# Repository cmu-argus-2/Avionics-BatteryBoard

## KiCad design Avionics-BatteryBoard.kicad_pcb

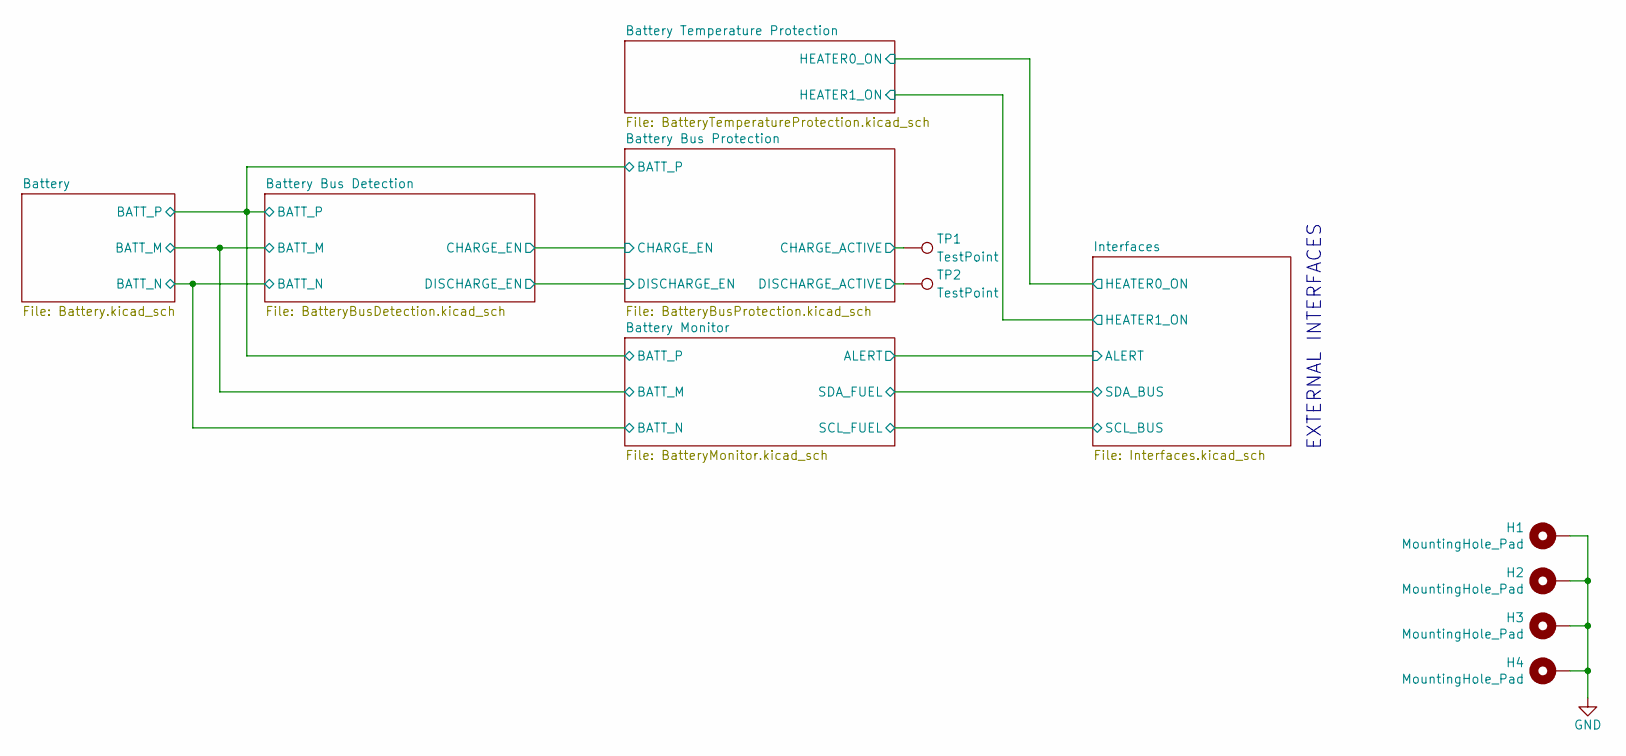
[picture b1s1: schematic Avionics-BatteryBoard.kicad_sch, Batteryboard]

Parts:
H1, H2, H3, H4: MountingHole_Pad; MountingHole_3.2mm_M3_Pad_Via
TP1, TP2: TestPoint; TestPoint_Pad_D1.5mm

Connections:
/Battery Bus Protection/CHARGE_ACTIVE: TP1.1 (1_1); also elsewhere on the board
/Battery Bus Protection/DISCHARGE_ACTIVE: TP2.1 (1_1); also elsewhere on the board
GND: H1.1 (1_1), H2.1 (1_1), H3.1 (1_1), H4.1 (1_1); also elsewhere on the board

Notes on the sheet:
EXTERNAL INTERFACES

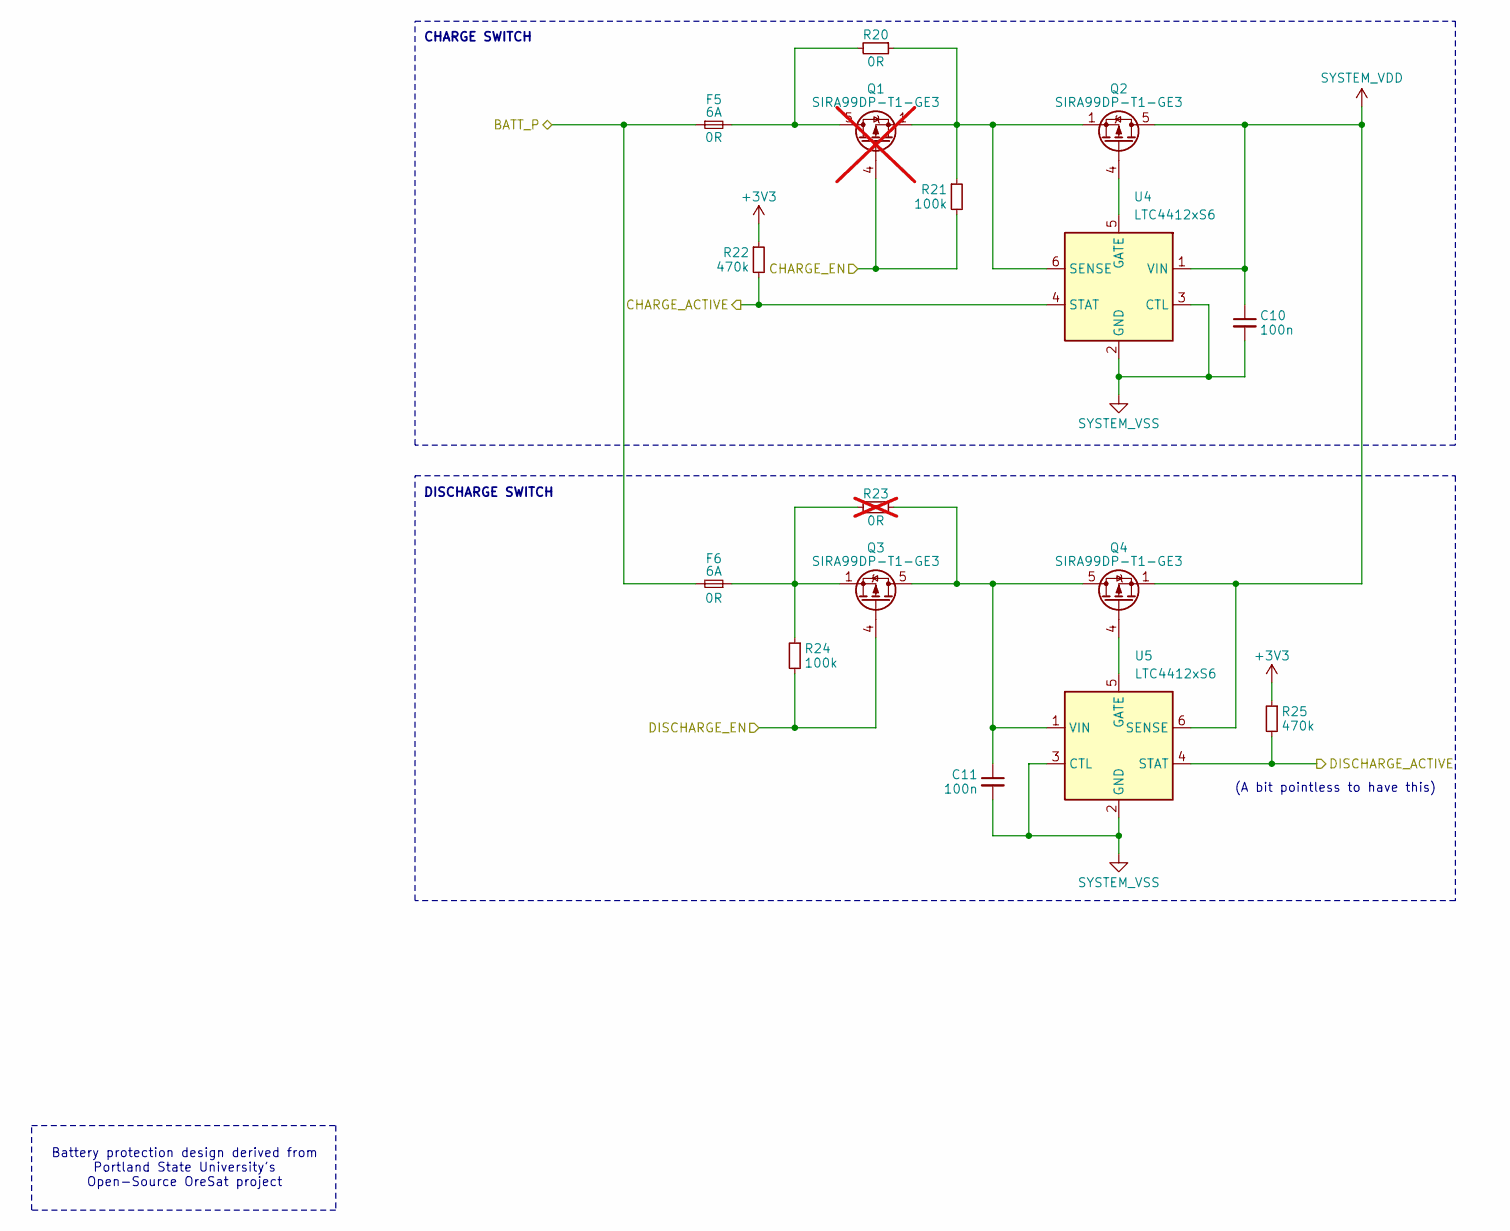
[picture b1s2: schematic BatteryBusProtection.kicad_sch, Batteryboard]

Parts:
C10, C11: 100n; C_0603_1608Metric; MPN C307348
F5, F6: 6A; Fuse_1206_3216Metric; MPN C844862
Q1: SIRA99DP-T1-GE3; PowerPAK_SO-8_Single; MPN C3289459; not fitted
Q2, Q3, Q4: SIRA99DP-T1-GE3; PowerPAK_SO-8_Single; MPN C3289459
R20: 0R; R_1206_3216Metric; MPN C237792
R21, R24: 100k; R_0603_1608Metric; MPN C237792
R22, R25: 470k; R_0603_1608Metric; MPN C138280
R23: 0R; R_1206_3216Metric; MPN C237792; not fitted
U4, U5: LTC4412xS6; TSOT-23-6

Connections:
+3V3: R22.1, R25.1; also elsewhere on the board
/Battery Bus Detection/BATT_P: F5.1, F6.2; also elsewhere on the board
/Battery Bus Detection/CHARGE_EN: Q1.4 (G), R21.2; also elsewhere on the board
/Battery Bus Detection/DISCHARGE_EN: Q3.4 (G), R24.2; also elsewhere on the board
/Battery Bus Protection/CHARGE_ACTIVE: R22.2, U4.4 (STAT); also elsewhere on the board
/Battery Bus Protection/DISCHARGE_ACTIVE: R25.2, U5.4 (STAT); also elsewhere on the board
unnamed: F6.1, Q3.1 (S), Q3.2 (S), Q3.3 (S), R23.2, R24.1
unnamed: F5.2, Q1.5 (D), R20.2
unnamed: Q2.4 (G), U4.5 (GATE)
unnamed: C11.1, Q3.5 (D), Q4.5 (D), R23.1, U5.1 (VIN)
unnamed: Q4.4 (G), U5.5 (GATE)
unnamed: Q1.1 (S), Q1.2 (S), Q1.3 (S), Q2.1 (S), Q2.2 (S), Q2.3 (S), R20.1, R21.1, U4.6 (SENSE)
SYSTEM_VDD: C10.1, Q2.5 (D), Q4.1 (S), Q4.2 (S), Q4.3 (S), U4.1 (VIN), U5.6 (SENSE); also elsewhere on the board
SYSTEM_VSS: C10.2, C11.2, U4.2 (GND), U4.3 (CTL), U5.2 (GND), U5.3 (CTL); also elsewhere on the board

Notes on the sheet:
CHARGE SWITCH
(A bit pointless to have this)
Battery protection design derived from Portland State University's Open-Source OreSat project
DISCHARGE SWITCH

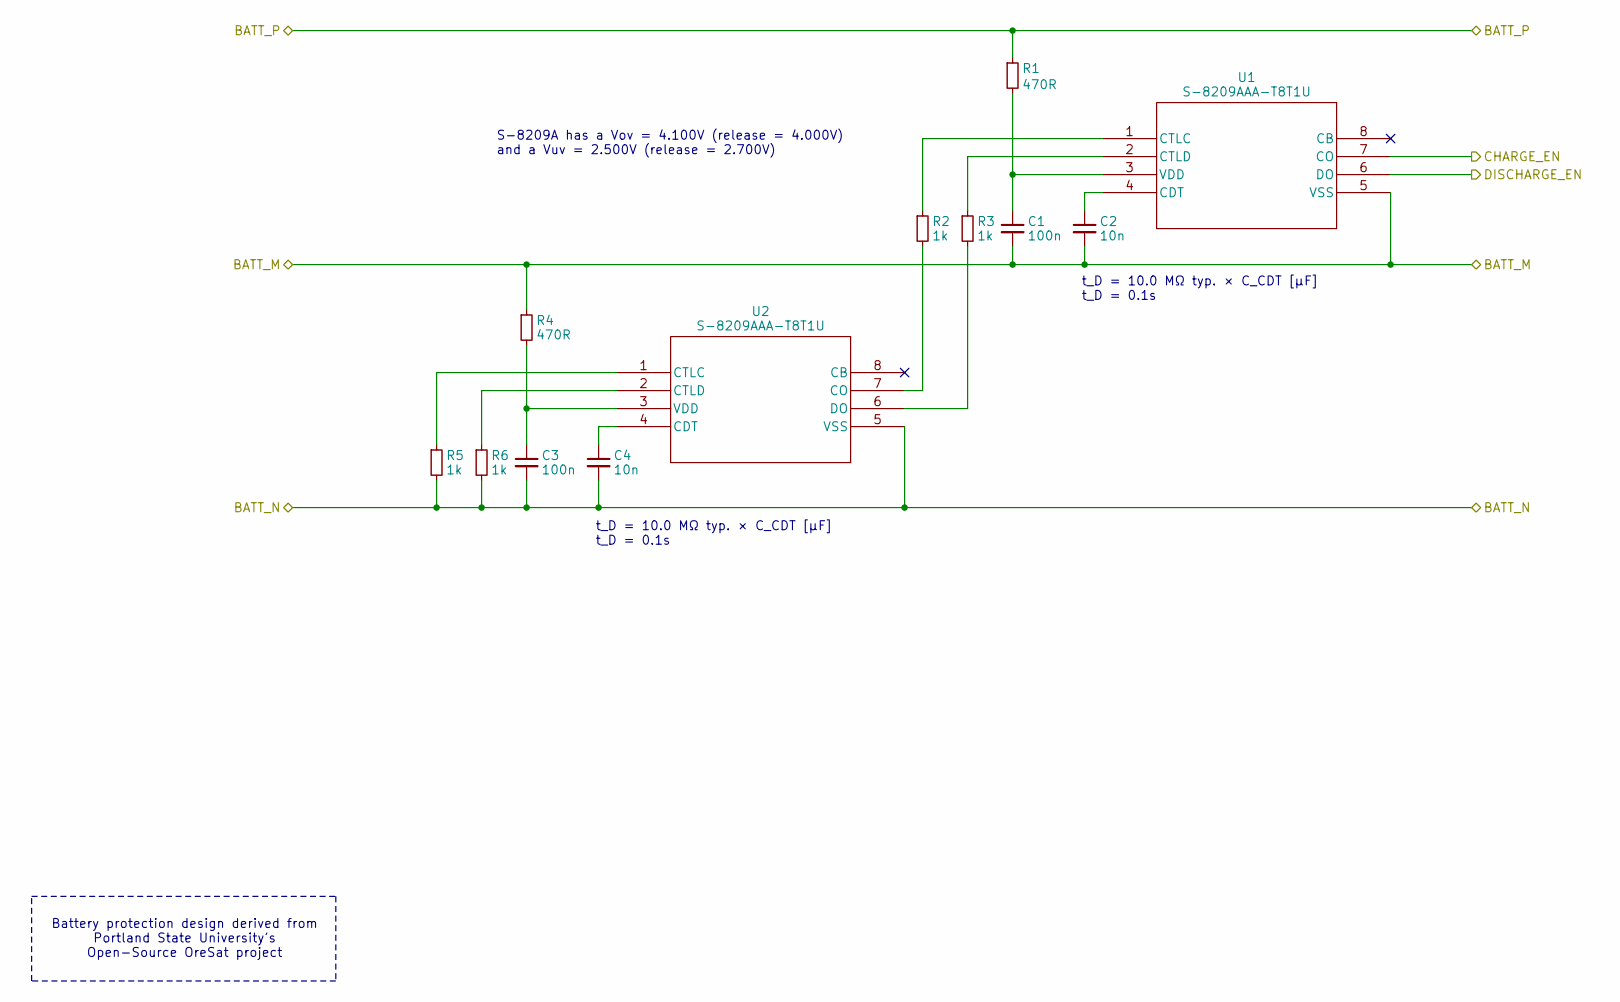
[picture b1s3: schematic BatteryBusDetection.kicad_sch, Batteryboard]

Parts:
C1, C3: 100n; C_0603_1608Metric; MPN C307348
C2, C4: 10n; C_0603_1608Metric; MPN C161232
R1, R4: 470R; R_0603_1608Metric; MPN C844564
R2, R3, R5, R6: 1k; R_0603_1608Metric; MPN C2484712
U1, U2: S-8209AAA-T8T1U; TSSOP8-E-PKG_FT008-A-P-SD-1.2_ABL

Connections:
/Battery Bus Detection/BATT_M: C1.2, C2.2, R4.1, U1.5 (VSS); also elsewhere on the board
/Battery Bus Detection/BATT_N: C3.2, C4.2, R5.2, R6.2, U2.5 (VSS); also elsewhere on the board
/Battery Bus Detection/BATT_P: R1.1; also elsewhere on the board
/Battery Bus Detection/CHARGE_EN: U1.7 (CO); also elsewhere on the board
/Battery Bus Detection/DISCHARGE_EN: U1.6 (DO); also elsewhere on the board
unnamed: C2.1, U1.4 (CDT)
unnamed: R2.1, U1.1 (CTLC)
unnamed: R3.1, U1.2 (CTLD)
unnamed: C1.1, R1.2, U1.3 (VDD)
unnamed: C4.1, U2.4 (CDT)
unnamed: R2.2, U2.7 (CO)
unnamed: R5.1, U2.1 (CTLC)
unnamed: R6.1, U2.2 (CTLD)
unnamed: R3.2, U2.6 (DO)
unnamed: C3.1, R4.2, U2.3 (VDD)

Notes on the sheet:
S-8209A has a Vov = 4.100V (release = 4.000V) and a Vuv = 2.500V (release = 2.700V)
t_D = 10.0 MΩ typ. × C_CDT [μF] t_D = 0.1s
Battery protection design derived from Portland State University's Open-Source OreSat project

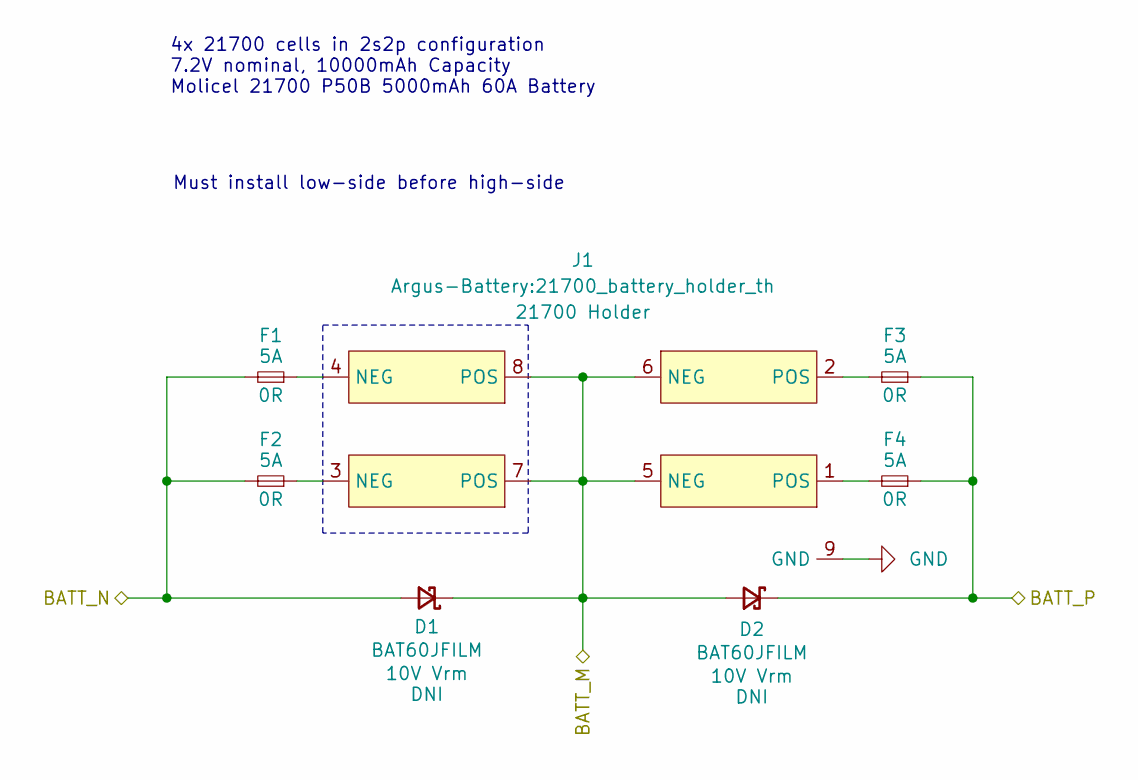
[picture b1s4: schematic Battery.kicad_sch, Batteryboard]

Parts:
D1, D2: BAT60JFILM; D_SOD-323_HandSoldering
F1, F2, F3, F4: 5A; Fuse_1206_3216Metric; MPN C844862
J1: 21700 Holder; 21700_battery_holder_th

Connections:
/Battery Bus Detection/BATT_M: D1.1 (K), D2.2 (A), J1.5 (NEG), J1.6 (NEG), J1.7 (POS), J1.8 (POS); also elsewhere on the board
/Battery Bus Detection/BATT_N: D1.2 (A), F1.2, F2.2; also elsewhere on the board
/Battery Bus Detection/BATT_P: D2.1 (K), F3.1, F4.1; also elsewhere on the board
GND: J1.9 (GND), J1.10 (GND), J1.11 (GND), J1.12 (GND); also elsewhere on the board
unnamed: F1.1, J1.4 (NEG)
unnamed: F2.1, J1.3 (NEG)
unnamed: F3.2, J1.2 (POS)
unnamed: F4.2, J1.1 (POS)

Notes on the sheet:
Must install low-side before high-side
4x 21700 cells in 2s2p configuration 7.2V nominal, 10000mAh Capacity Molicel 21700 P50B 5000mAh 60A Battery

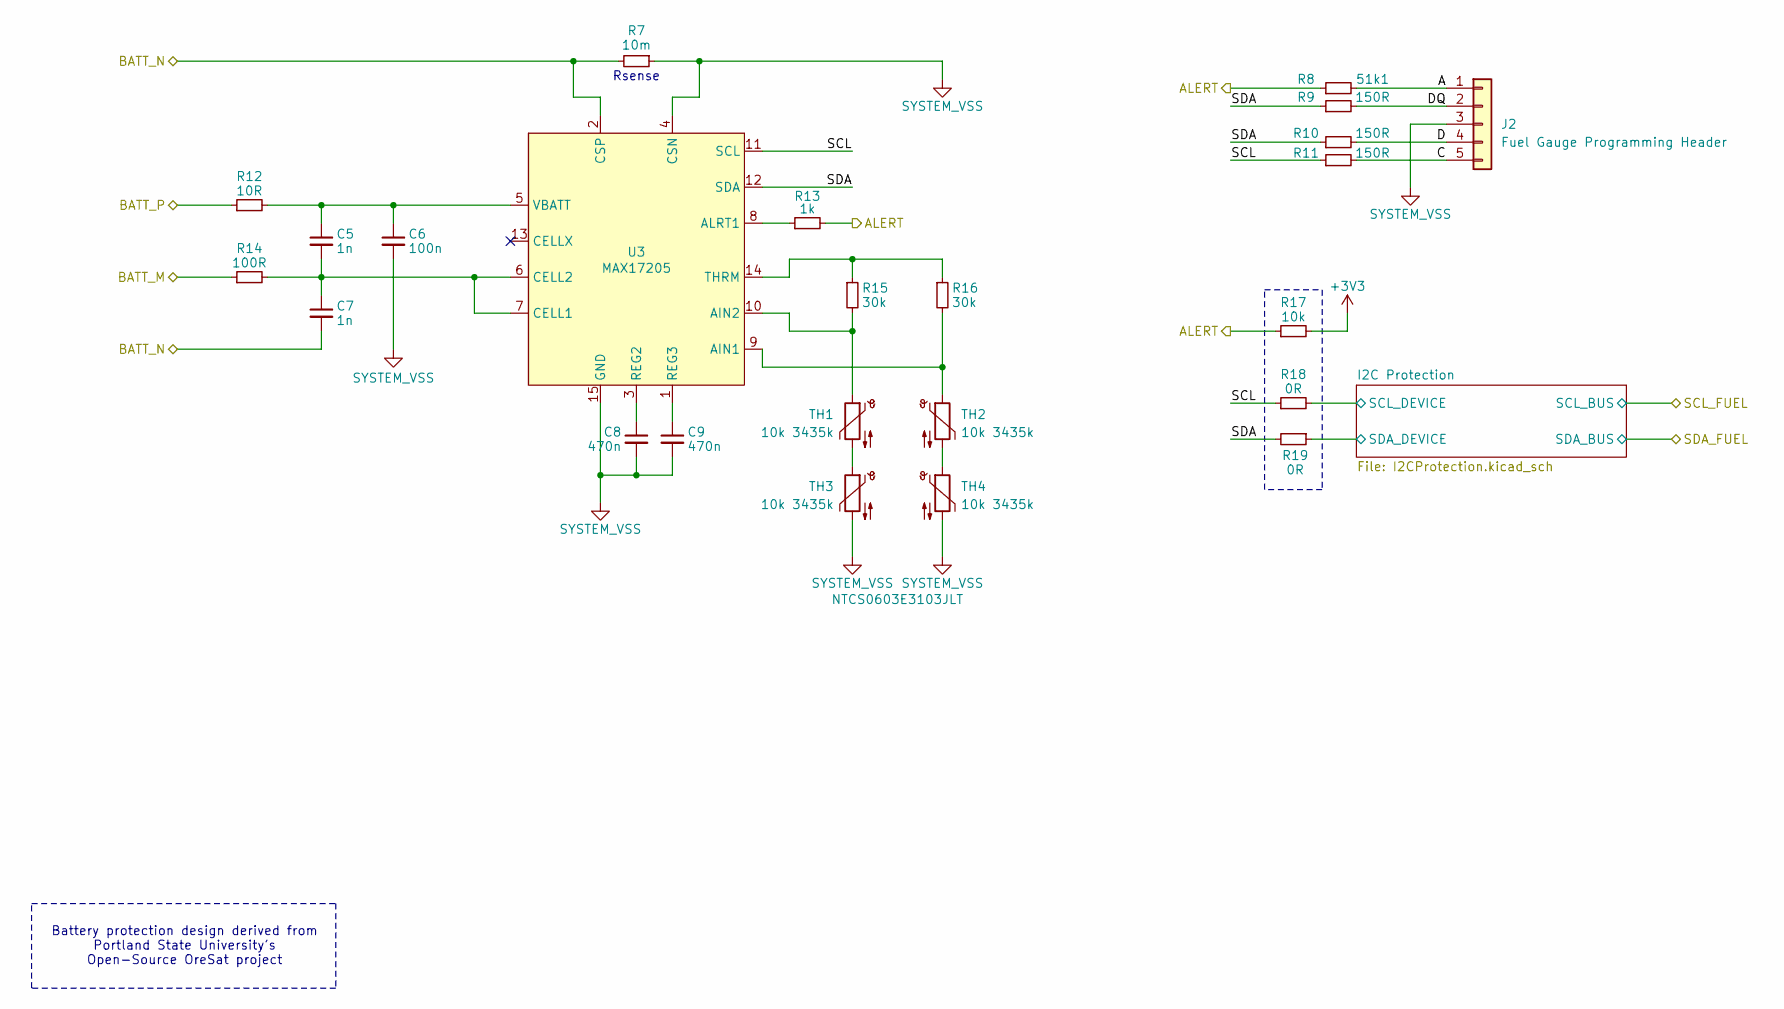
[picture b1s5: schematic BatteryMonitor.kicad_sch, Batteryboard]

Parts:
C5, C7: 1n; C_0603_1608Metric; MPN C161231
C6: 100n; C_0603_1608Metric; MPN C307348
C8, C9: 470n; C_0603_1608Metric; MPN C472773
J2: Fuel Gauge Programming Header; PinHeader_1x05_P2.54mm_Vertical_SMD_Pin1Left
R7: 10m; R_2512_6332Metric; MPN C840621
R8: 51k1; R_0603_1608Metric; MPN C844575
R9, R10, R11: 150R; R_0603_1608Metric; MPN C844741
R12: 10R; R_0603_1608Metric; MPN C3029194
R13: 1k; R_0603_1608Metric; MPN C2484712
R14: 100R; R_0603_1608Metric; MPN C844917
R15, R16: 30k; R_0603_1608Metric; MPN C844774
R17: 10k; R_0603_1608Metric; MPN C2479067
R18, R19: 0R; R_0603_1608Metric; MPN C844915
TH1, TH2, TH3, TH4: 10k 3435k; C_0603_1608Metric
U3: MAX17205; TDFN-14-1EP_3x3mm_P0.4mm_EP1.78x2.35mm; MPN C401140

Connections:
+3V3: R17.2; also elsewhere on the board
/Battery Bus Detection/BATT_M: R14.1; also elsewhere on the board
/Battery Bus Detection/BATT_N: C7.2, R7.2, U3.2 (CSP); also elsewhere on the board
/Battery Bus Detection/BATT_P: R12.1; also elsewhere on the board
/Battery Monitor/A: J2.1, R8.2
/Battery Monitor/C: J2.5, R11.2
/Battery Monitor/D: J2.4, R10.2
/Battery Monitor/DQ: J2.2, R9.2
/Battery Monitor/I2C Protection/SCL_DEVICE: R18.2; also elsewhere on the board
/Battery Monitor/I2C Protection/SDA_DEVICE: R19.1; also elsewhere on the board
/Battery Monitor/SCL: R11.1, R18.1, U3.11 (SCL)
/Battery Monitor/SDA: R9.1, R10.1, R19.2, U3.12 (SDA)
/Interfaces/ALERT: R8.1, R13.2, R17.1; also elsewhere on the board
unnamed: TH1.2, TH3.1
unnamed: TH2.2, TH4.1
unnamed: R16.2, TH2.1, U3.9 (AIN1)
unnamed: R15.2, TH1.1, U3.10 (AIN2)
unnamed: R13.1, U3.8 (ALRT1)
unnamed: C5.2, C7.1, R14.2, U3.6 (CELL2), U3.7 (CELL1)
unnamed: C8.1, U3.3 (REG2)
unnamed: C9.1, U3.1 (REG3)
unnamed: R15.1, R16.1, U3.14 (THRM)
unnamed: C5.1, C6.1, R12.2, U3.5 (VBATT)
SYSTEM_VSS: C6.2, C8.2, C9.2, J2.3, R7.1, TH3.2, TH4.2, U3.4 (CSN), U3.15 (GND); also elsewhere on the board

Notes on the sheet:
Rsense
Battery protection design derived from Portland State University's Open-Source OreSat project

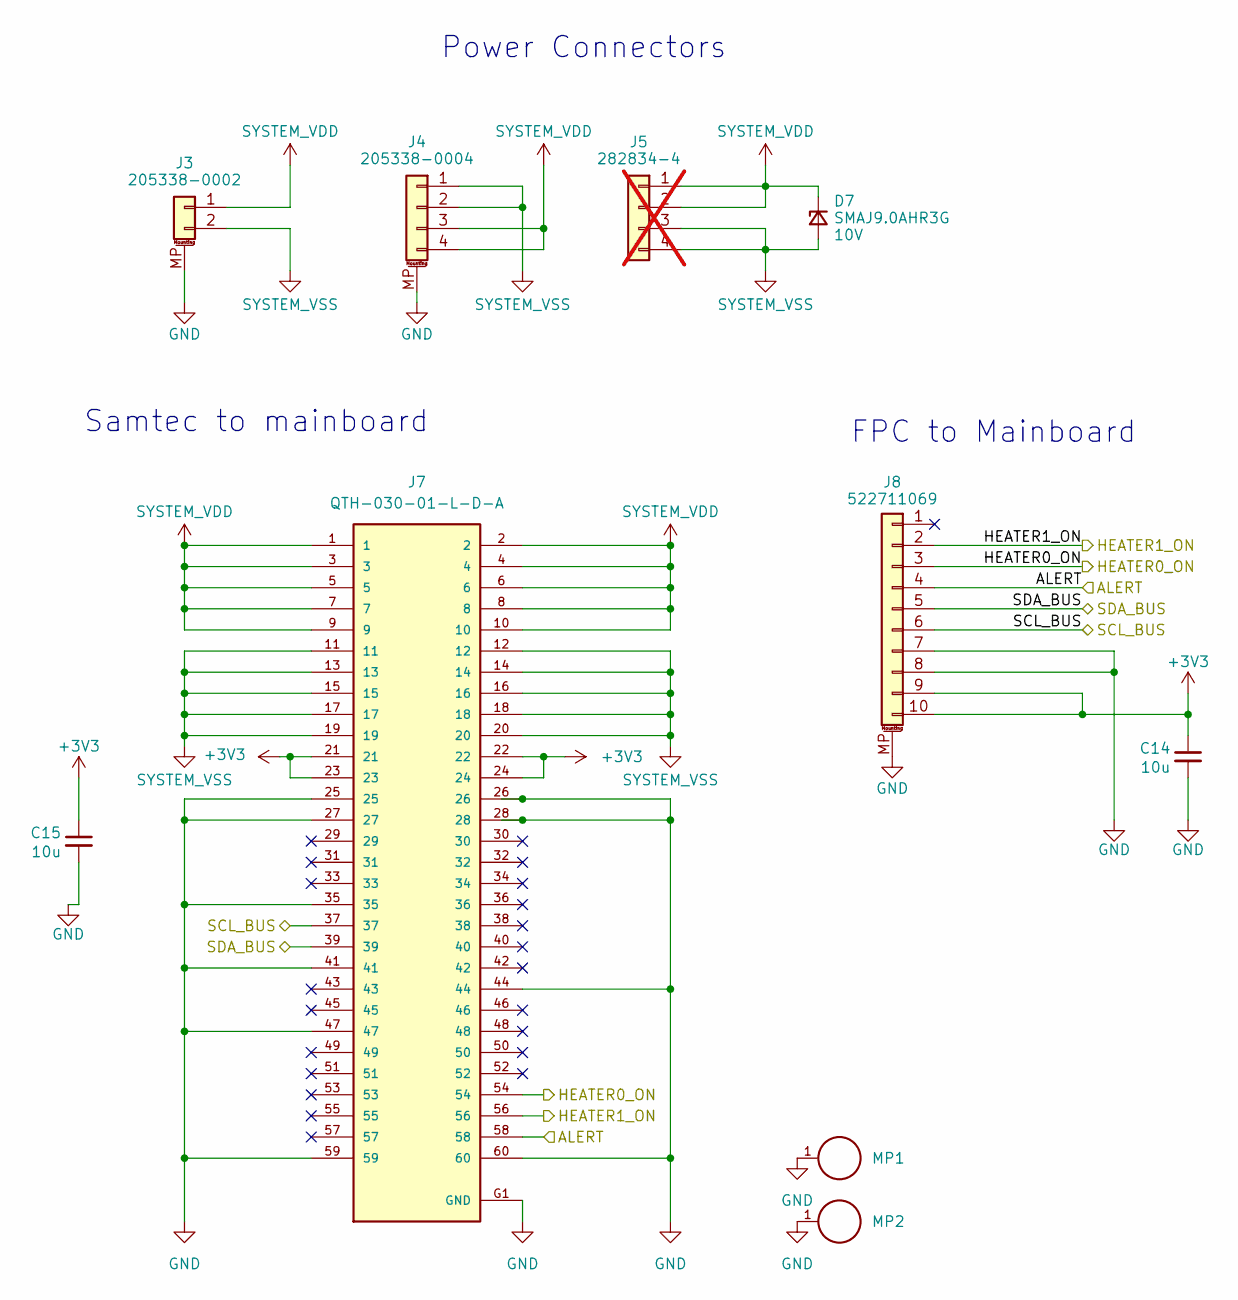
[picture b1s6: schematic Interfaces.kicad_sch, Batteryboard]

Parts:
C14, C15: 10u; C_0805_2012Metric; MPN C386084
D7: SMAJ9.0AHR3G; D_SMA; Part 10V
J3: 205338-0002; Molex_Pico-Lock_205338-0002_1x02-1MP_P2.00mm_Horizontal; MPN C17575002
J4: 205338-0004; Molex_Pico-Lock_205338-0004_1x04-1MP_P2.00mm_Horizontal; MPN C916325
J5: 282834-4; TerminalBlock_TE_282834-4_1x04_P2.54mm_Horizontal; not fitted
J7: QTH-030-01-L-D-A; SAMTEC-QTH-030-01-L-D-A; PARTREV BJ
J8: 522711069; CON_522711069_MOL; MPN C588180
MP1, MP2: M3 x 5mm; WA-SMSI_9774050360; PART-NUMBER 9774050360R

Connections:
+3V3: C14.1, C15.1, J7.21, J7.22, J7.23, J7.24, J8.9, J8.10; also elsewhere on the board
/Interfaces/ALERT: J7.58, J8.4; also elsewhere on the board
/Interfaces/HEATER0_ON: J7.54, J8.3; also elsewhere on the board
/Interfaces/HEATER1_ON: J7.56, J8.2; also elsewhere on the board
/Interfaces/SCL_BUS: J7.37, J8.6; also elsewhere on the board
/Interfaces/SDA_BUS: J7.39, J8.5; also elsewhere on the board
GND: C14.2, C15.2, J3.MP (MountPin), J4.MP (MountPin), J7.25, J7.26, J7.27, J7.28, J7.35, J7.41, J7.44, J7.47, J7.59, J7.60, J7.G1 (GND), J7.G2 (GND), J7.G3 (GND), J7.G4 (GND), J8.7, J8.8, J8.MP (MountPin), MP1.1, MP2.1; also elsewhere on the board
SYSTEM_VDD: D7.1 (K), J3.1, J4.3, J4.4, J5.1, J5.2, J7.1, J7.2, J7.3, J7.4, J7.5, J7.6, J7.7, J7.8, J7.9, J7.10; also elsewhere on the board
SYSTEM_VSS: D7.2 (A), J3.2, J4.1, J4.2, J5.3, J5.4, J7.11, J7.12, J7.13, J7.14, J7.15, J7.16, J7.17, J7.18, J7.19, J7.20; also elsewhere on the board

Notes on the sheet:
FPC to Mainboard
Samtec to mainboard
Power Connectors

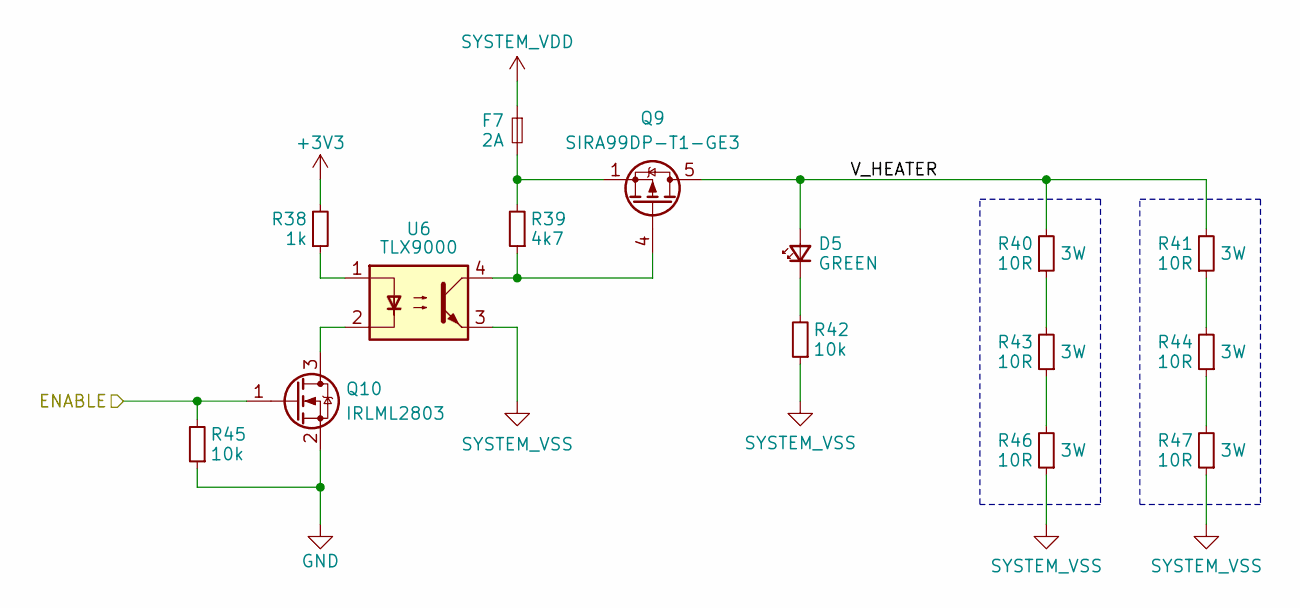
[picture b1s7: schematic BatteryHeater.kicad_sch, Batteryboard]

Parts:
D5: GREEN; LED_0603_1608Metric; MPN C2909774
F7: 2A; Fuse_1206_3216Metric
Q9: SIRA99DP-T1-GE3; PowerPAK_SO-8_Single; MPN C3289459
Q10: IRLML2803; SOT-23; MPN C2590
R38: 1k; R_0603_1608Metric; MPN C2479067
R39: 4k7; R_0603_1608Metric; MPN C2479067
R40, R41, R43, R44, R46, R47: 10R; R_2512_6332Metric
R42, R45: 10k; R_0603_1608Metric; MPN C2479067
U6: TLX9000; SOIC-4_4.55x2.6mm_P1.27mm

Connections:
+3V3: R38.2; also elsewhere on the board
/Battery Temperature Protection/BatteryHeater1/V_HEATER: D5.2 (A), Q9.5 (D), R40.2, R41.2
/Interfaces/HEATER1_ON: Q10.1 (G), R45.2; also elsewhere on the board
GND: Q10.2 (S), R45.1; also elsewhere on the board
unnamed: D5.1 (K), R42.2
unnamed: F7.2, Q9.1 (S), Q9.2 (S), Q9.3 (S), R39.2
unnamed: Q9.4 (G), R39.1, U6.4
unnamed: Q10.3 (D), U6.2
unnamed: R38.1, U6.1
unnamed: R40.1, R43.2
unnamed: R41.1, R44.2
unnamed: R43.1, R46.2
unnamed: R44.1, R47.2
SYSTEM_VDD: F7.1; also elsewhere on the board
SYSTEM_VSS: R42.1, R46.1, R47.1, U6.3; also elsewhere on the board

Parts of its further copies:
D6: GREEN; LED_0603_1608Metric; MPN C2909774
F8: 2A; Fuse_1206_3216Metric
Q11: SIRA99DP-T1-GE3; PowerPAK_SO-8_Single; MPN C3289459
Q12: IRLML2803; SOT-23; MPN C2590
R48: 1k; R_0603_1608Metric; MPN C2479067
R49: 4k7; R_0603_1608Metric; MPN C2479067
R50, R51, R53, R54, R56, R57: 10R; R_2512_6332Metric
R52, R55: 10k; R_0603_1608Metric; MPN C2479067
U7: TLX9000; SOIC-4_4.55x2.6mm_P1.27mm

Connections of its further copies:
+3V3: R48.2; also elsewhere on the board
/Battery Temperature Protection/BatteryHeater/V_HEATER: D6.2 (A), Q11.5 (D), R50.2, R51.2
/Interfaces/HEATER0_ON: Q12.1 (G), R55.2; also elsewhere on the board
GND: Q12.2 (S), R55.1; also elsewhere on the board
unnamed: D6.1 (K), R52.2
unnamed: F8.2, Q11.1 (S), Q11.2 (S), Q11.3 (S), R49.2
unnamed: Q11.4 (G), R49.1, U7.4
unnamed: Q12.3 (D), U7.2
unnamed: R48.1, U7.1
unnamed: R50.1, R53.2
unnamed: R51.1, R54.2
unnamed: R53.1, R56.2
unnamed: R54.1, R57.2
SYSTEM_VDD: F8.1; also elsewhere on the board
SYSTEM_VSS: R52.1, R56.1, R57.1, U7.3; also elsewhere on the board

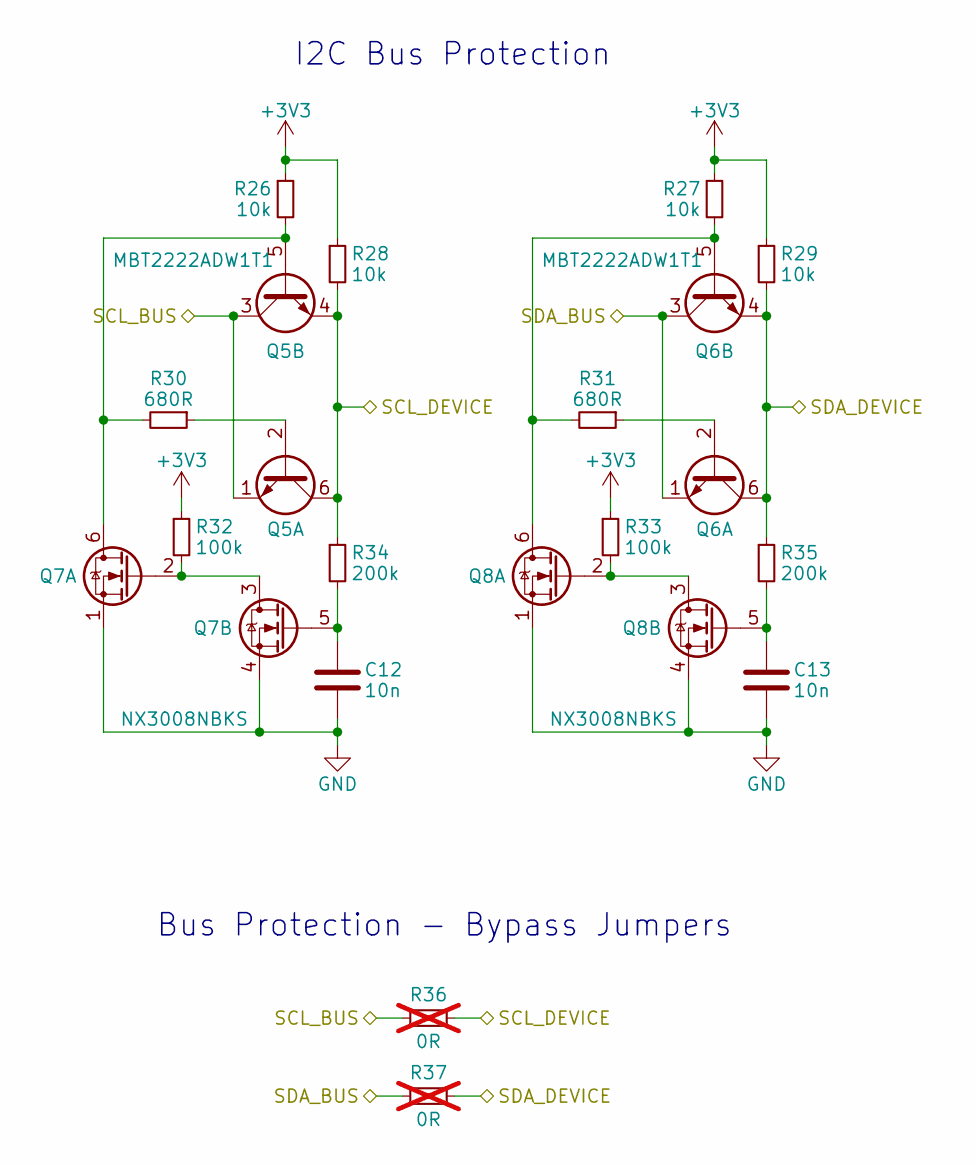
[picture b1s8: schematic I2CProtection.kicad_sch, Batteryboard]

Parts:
C12, C13: 10n; C_0603_1608Metric; MPN C161232
Q5, Q6: MBT2222ADW1T1; SOT-363_SC-70-6; Manufacturer_Part_Number MBT2222ADW1T1G
Q7, Q8: NX3008NBKS; SOT-363_SC-70-6; MPN C3280240
R26, R27, R28, R29: 10k; R_0603_1608Metric; MPN C2479067
R30, R31: 680R; R_0603_1608Metric; MPN C844802
R32, R33: 100k; R_0603_1608Metric; MPN C237792
R34, R35: 200k; R_0603_1608Metric; MPN C118142
R36, R37: 0R; R_0603_1608Metric; not fitted

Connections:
+3V3: R26.1, R27.1, R28.1, R29.1, R32.1, R33.1; also elsewhere on the board
/Battery Monitor/I2C Protection/SCL_DEVICE: Q5.4 (E2), Q5.6 (C1), R28.2, R34.1, R36.1; also elsewhere on the board
/Battery Monitor/I2C Protection/SDA_DEVICE: Q6.4 (E2), Q6.6 (C1), R29.2, R35.1, R37.1; also elsewhere on the board
/Interfaces/SCL_BUS: Q5.1 (E1), Q5.3 (C2), R36.2; also elsewhere on the board
/Interfaces/SDA_BUS: Q6.1 (E1), Q6.3 (C2), R37.2; also elsewhere on the board
GND: C12.2, C13.2, Q7.1 (S), Q7.4 (S), Q8.1 (S), Q8.4 (S); also elsewhere on the board
unnamed: Q5.2 (B1), R30.1
unnamed: Q5.5 (B2), Q7.6 (D), R26.2, R30.2
unnamed: Q6.2 (B1), R31.1
unnamed: Q6.5 (B2), Q8.6 (D), R27.2, R31.2
unnamed: Q7.2 (G), Q7.3 (D), R32.2
unnamed: C12.1, Q7.5 (G), R34.2
unnamed: Q8.2 (G), Q8.3 (D), R33.2
unnamed: C13.1, Q8.5 (G), R35.2

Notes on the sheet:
I2C Bus Protection
Bus Protection - Bypass Jumpers

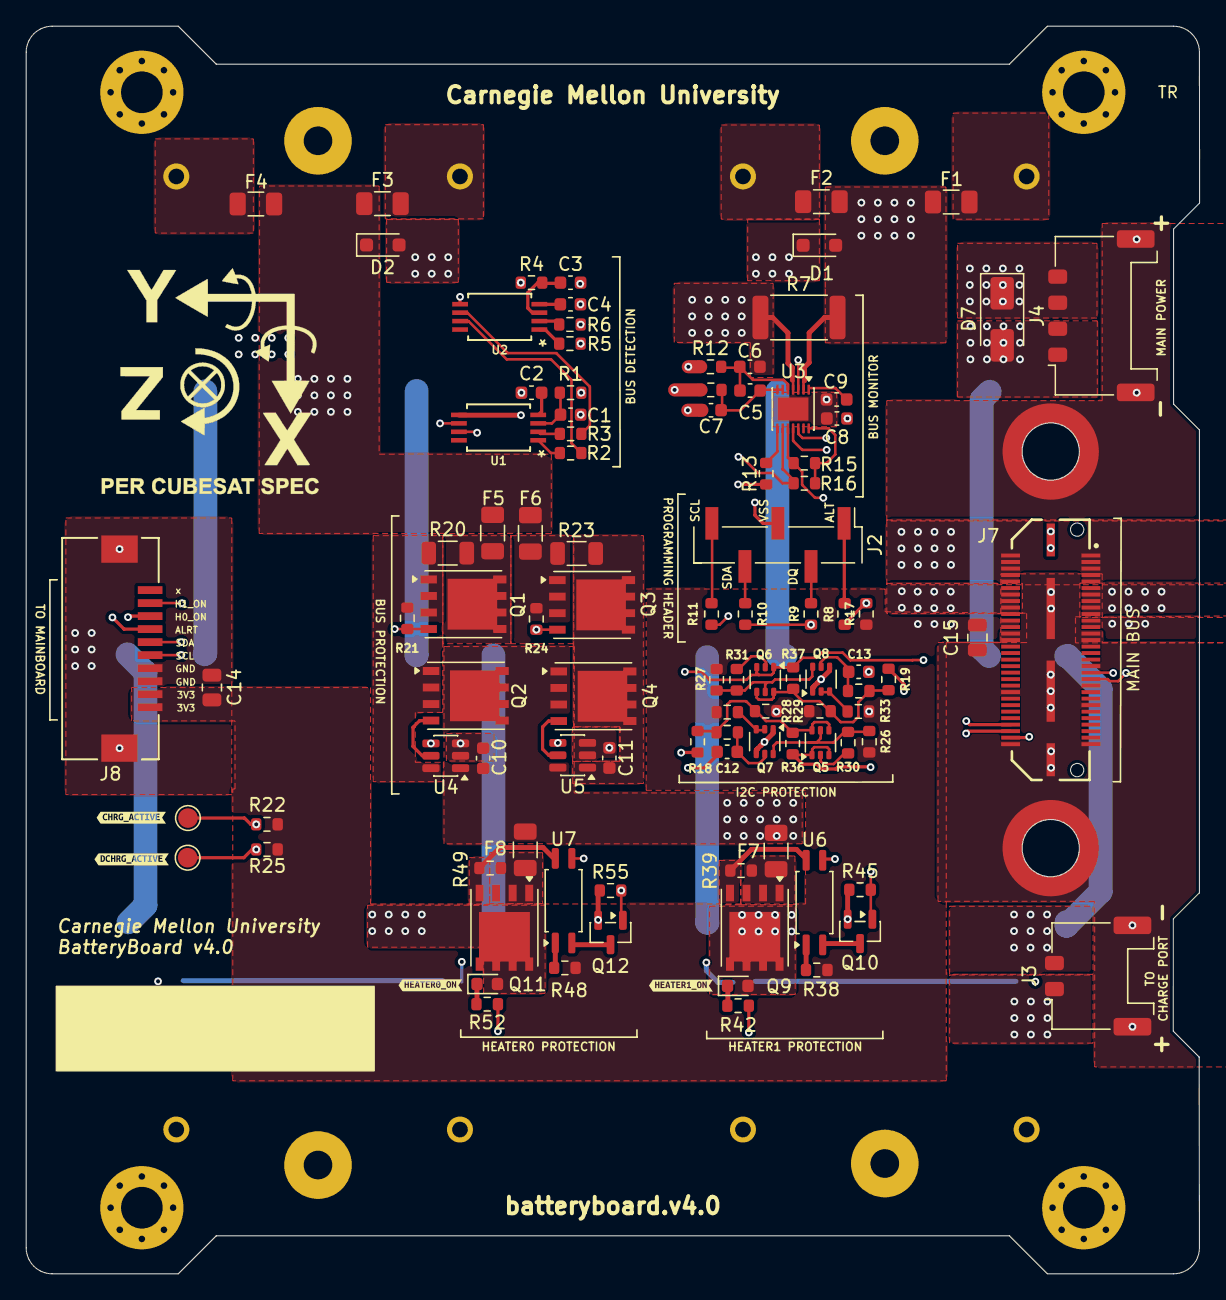
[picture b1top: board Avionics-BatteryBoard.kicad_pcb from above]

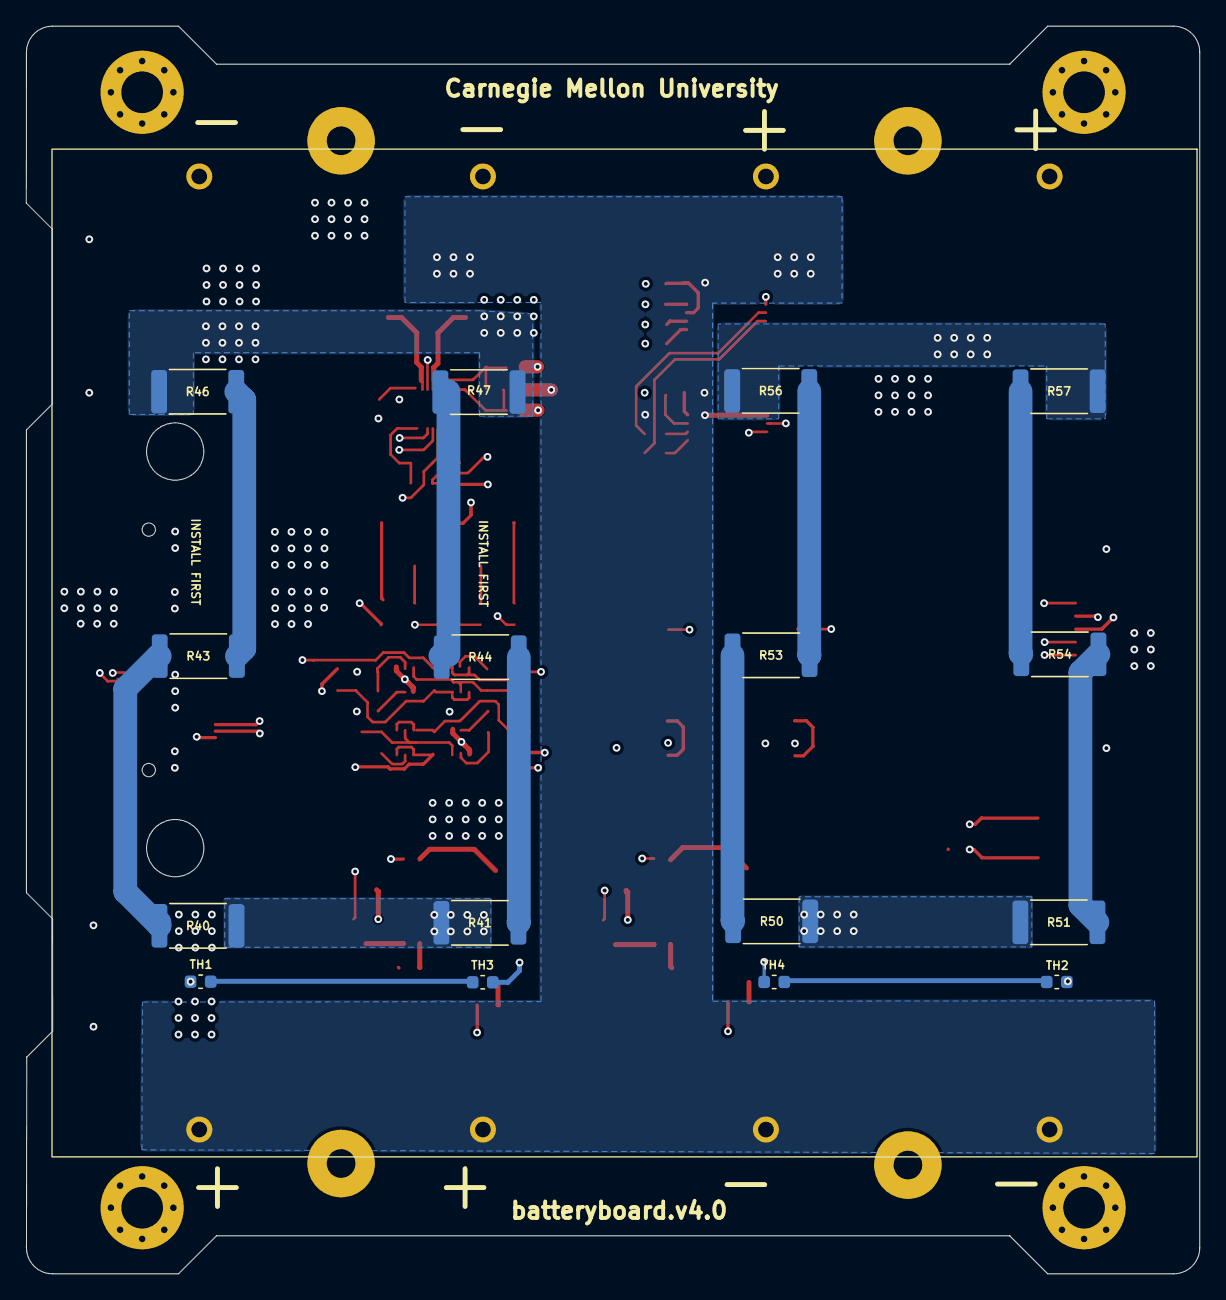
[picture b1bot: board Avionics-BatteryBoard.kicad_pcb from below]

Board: 4 copper layers, 90.2 x 95.9 mm, 126 parts (17 on the bottom side), 82 nets.

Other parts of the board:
kibuzzard-6A91DD5B: G***; kibuzzard-6A91DD5B
kibuzzard-6A91DD42: G***; kibuzzard-6A91DD42
kibuzzard-6A825BB0: G***; kibuzzard-6A825BB0
kibuzzard-6A825BF2: G***; kibuzzard-6A825BF2

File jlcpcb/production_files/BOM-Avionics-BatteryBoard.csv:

Comment,Designator,Footprint,LCSC,Quantity
205338-0004,J4,Molex_Pico-Lock_205338-0004_1x04-1MP_P2.00mm_Horizontal,,1
SMAJ9.0AHR3G,D7,D_SMA,,1
S-8209AAA-T8T1U,U2,TSSOP8-E-PKG_FT008-A-P-SD-1.2_ABL,,1
4k7,R49,R_0603_1608Metric,,1
470k,R25,R_0603_1608Metric,,1
205338-0002,J3,Molex_Pico-Lock_205338-0002_1x02-1MP_P2.00mm_Horizontal,,1
100n,C1,C_0603_1608Metric,,1
10k,R27,R_0603_1608Metric,,1
680R,R30,R_0603_1608Metric,,1
1k,R6,R_0603_1608Metric,,1
10k,R26,R_0603_1608Metric,,1
150R,R9,R_0603_1608Metric,,1
150R,R10,R_0603_1608Metric,,1
10k,R45,R_0603_1608Metric,,1
100R,R14,R_0603_1608Metric,,1
MAX17205,U3,TDFN-14-1EP_3x3mm_P0.4mm_EP1.78x2.35mm,,1
QTH-030-01-L-D-A,J7,SAMTEC-QTH-030-01-L-D-A,,1
51k1,R8,R_0603_1608Metric,,1
200k,R34,R_0603_1608Metric,,1
470R,R4,R_0603_1608Metric,,1
2A,F7,Fuse_1206_3216Metric,,1
NX3008NBKS,Q8,SOT-363_SC-70-6,,1
10R,R12,R_0603_1608Metric,,1
1n,C5,C_0603_1608Metric,,1
10n,C12,C_0603_1608Metric,,1
100n,C6,C_0603_1608Metric,,1
470k,R22,R_0603_1608Metric,,1
10k,R42,R_0603_1608Metric,,1
10n,C4,C_0603_1608Metric,,1
LTC4412xS6,U5,TSOT-23-6,,1
GREEN,D6,LED_0603_1608Metric,,1
MBT2222ADW1T1,Q5,SOT-363_SC-70-6,,1
LTC4412xS6,U4,TSOT-23-6,,1
100k,R33,R_0603_1608Metric,,1
SIRA99DP-T1-GE3,Q4,PowerPAK_SO-8_Single,,1
10k,R17,R_0603_1608Metric,,1
680R,R31,R_0603_1608Metric,,1
TLX9000,U7,SOIC-4_4.55x2.6mm_P1.27mm,,1
100k,R32,R_0603_1608Metric,,1
TLX9000,U6,SOIC-4_4.55x2.6mm_P1.27mm,,1
10k,R55,R_0603_1608Metric,,1
10u,C14,C_0805_2012Metric,,1
6A,F5,Fuse_1206_3216Metric,,1
2A,F8,Fuse_1206_3216Metric,,1
1k,R38,R_0603_1608Metric,,1
5A,F3,Fuse_1206_3216Metric,,1
100n,C3,C_0603_1608Metric,,1
30k,R16,R_0603_1608Metric,,1
100n,C10,C_0603_1608Metric,,1
522711069,J8,CON_522711069_MOL,,1
470n,C9,C_0603_1608Metric,,1
200k,R35,R_0603_1608Metric,,1
5A,F2,Fuse_1206_3216Metric,,1
SIRA99DP-T1-GE3,Q3,PowerPAK_SO-8_Single,,1
M3 x 5mm,MP2,WA-SMSI_9774050360,,1
10k,R28,R_0603_1608Metric,,1
100k,R21,R_0603_1608Metric,,1
1k,R2,R_0603_1608Metric,,1
SIRA99DP-T1-GE3,Q11,PowerPAK_SO-8_Single,,1
470R,R1,R_0603_1608Metric,,1
470n,C8,C_0603_1608Metric,,1
0R,R18,R_0603_1608Metric,,1
10k,R29,R_0603_1608Metric,,1
5A,F4,Fuse_1206_3216Metric,,1
10n,C13,C_0603_1608Metric,,1
100n,C11,C_0603_1608Metric,,1
10m,R7,R_2512_6332Metric,,1
1k,R48,R_0603_1608Metric,,1
BAT60JFILM,D2,D_SOD-323_HandSoldering,,1
0R,R19,R_0603_1608Metric,,1
S-8209AAA-T8T1U,U1,TSSOP8-E-PKG_FT008-A-P-SD-1.2_ABL,,1
1k,R3,R_0603_1608Metric,,1
1k,R13,R_0603_1608Metric,,1
SIRA99DP-T1-GE3,Q2,PowerPAK_SO-8_Single,,1
M3 x 5mm,MP1,WA-SMSI_9774050360,,1
0R,R20,R_1206_3216Metric,,1
30k,R15,R_0603_1608Metric,,1
NX3008NBKS,Q7,SOT-363_SC-70-6,,1
10k,R52,R_0603_1608Metric,,1
10u,C15,C_0805_2012Metric,,1
100k,R24,R_0603_1608Metric,,1
150R,R11,R_0603_1608Metric,,1
4k7,R39,R_0603_1608Metric,,1
IRLML2803,Q12,SOT-23,,1
5A,F1,Fuse_1206_3216Metric,,1
6A,F6,Fuse_1206_3216Metric,,1
1n,C7,C_0603_1608Metric,,1
1k,R5,R_0603_1608Metric,,1
MBT2222ADW1T1,Q6,SOT-363_SC-70-6,,1
BAT60JFILM,D1,D_SOD-323_HandSoldering,,1
Fuel Gauge Programming Header,J2,PinHeader_1x05_P2.54mm_Vertical_SMD_Pin1Left,,1
10n,C2,C_0603_1608Metric,,1
IRLML2803,Q10,SOT-23,,1
GREEN,D5,LED_0603_1608Metric,,1
SIRA99DP-T1-GE3,Q9,PowerPAK_SO-8_Single,,1
10R,R40,R_2512_6332Metric,,1
10R,R57,R_2512_6332Metric,,1
10R,R44,R_2512_6332Metric,,1
10k 3435k,TH1,C_0603_1608Metric,,1
10k 3435k,TH2,C_0603_1608Metric,,1
10R,R41,R_2512_6332Metric,,1
10R,R50,R_2512_6332Metric,,1
10R,R46,R_2512_6332Metric,,1
10R,R54,R_2512_6332Metric,,1
10k 3435k,TH4,C_0603_1608Metric,,1
10R,R56,R_2512_6332Metric,,1
10k 3435k,TH3,C_0603_1608Metric,,1
10R,R47,R_2512_6332Metric,,1
10R,R51,R_2512_6332Metric,,1
10R,R53,R_2512_6332Metric,,1
10R,R43,R_2512_6332Metric,,1
